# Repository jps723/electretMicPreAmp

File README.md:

# Electret Mic Preamp Build Notes 2/24/20

This project is in partnership with [Bantam Tools](https://www.bantamtools.com)

**Design Notes:**

This Electret Mic Preamp is a passive preamplifier and is based around the [LM358 op amp](https://www.ti.com/product/LM358).  This is a dual operational amplifier where in this circuit we are utilizing only one of the amplifiers on pins 1, 2, and 3.  Pin 4 is the Ground, where pin 8 is VCC.  

Pin 8 is powered by a 5v source, through two capacitors for filtering out high/low level noise (C2 and C3).  The electret mic is powered through a 10k resistor (R1), where the signal then goes through a coupling capacitor (C1) before a 1k resistor (R2) and entering pin 2.  A 200k variable resistor (VR1) serves to create feedback and the relationship between R2 and VR1 establishes the potential gain of the signal being represented by Gain = VR1/R2.  In this circuit, there is a potential gain of up to 200x the original signal (200k/1k = 200), allowing for a wide range of adjustment.

Two 100k resistors (R4/R5) are connected to GND and VCC respectively, prior to connecting to pin 3, for setting the potential voltage (2.5v). The circuit also has a power indicating LED for showing that the unit is powered on.

# Build Process
**Bits:**
1/32”
1/64”
**Mill Time:**
6m15s

It’s easiest to solder in this order:
```
1. Resistors
2. Ceramic Caps
3. Electret Mic
4. Dip Socket
5. LED
6. Electrolytic Caps
7. Screw Terminal
8. Potentiometer
```

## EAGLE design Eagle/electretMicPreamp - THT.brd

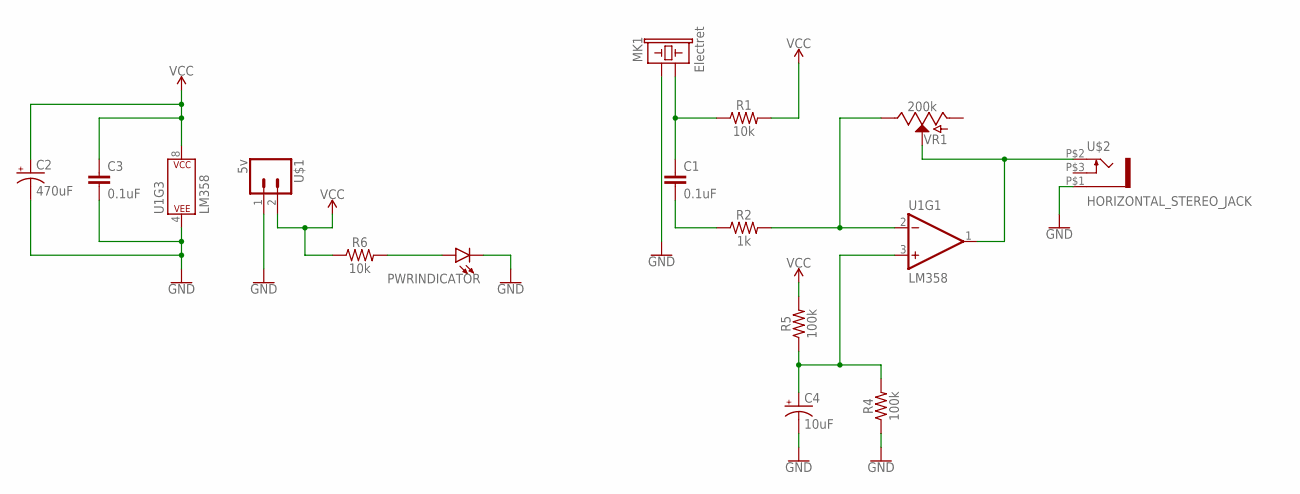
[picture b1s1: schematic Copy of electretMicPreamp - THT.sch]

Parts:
C1, C3: 0.1uF; CAP-PTH-SMALL-KIT
C2: 470uF; CPOL-RADIAL-2.5MM-5MM
C4: 10uF; CPOL-RADIAL-2.5MM-5MM
MK1: Electret; MICROPHONE-PTH-9.7MM
PWRINDICATOR: LED-3MM-NO_SILK; LED_3MM-NS
R1, R6: 10k; AXIAL-0.3
R2: 1k; AXIAL-0.3
R4, R5: 100k; AXIAL-0.3
U1: LM358; DIP08-KIT
U$1: 5v; SCREWTERMINAL-2X1
U$2: HORIZONTAL_STEREO_JACK
VR1: 200k; POT-PTH-ALPS

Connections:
GND: C2.2 (-), C3.2, C4.2 (-), MK1.1, PWRINDICATOR.K (C), R4.P$1 (1), U1.4 (P$V-), U$1.1, U$2.P$1 (1)
unnamed: C1.1, MK1.2, R1.P$1 (1)
unnamed: C1.2, R2.P$1 (1)
unnamed: R2.P$2 (2), U1.2 (-IN), VR1.P$1 (E)
unnamed: U1.1 (OUT), U$2.P$2 (2), VR1.P$2 (S)
unnamed: PWRINDICATOR.A, R6.P$2 (2)
unnamed: C4.1 (+), R4.P$2 (2), R5.P$1 (1), U1.3 (+IN)
VCC: C2.1 (+), C3.1, R1.P$2 (2), R5.P$2 (2), R6.P$1 (1), U1.8 (P$V+), U$1.2

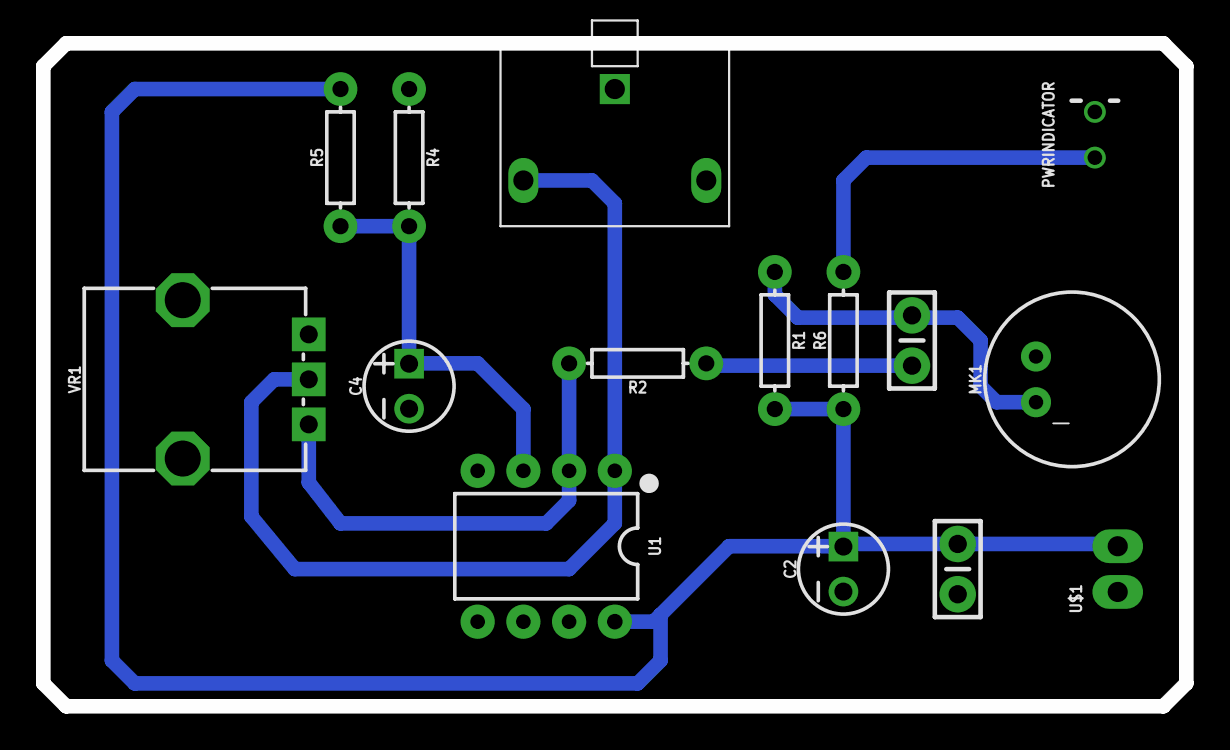
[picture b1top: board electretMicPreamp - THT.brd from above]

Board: 2 copper layers, 63.5 x 36.8 mm, 15 parts (0 on the bottom side), 8 nets.

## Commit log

2020-10-30 added bantam tools credit

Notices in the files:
parts and their libraries:
SparkFun-Retired: Licensing: Creative Commons ShareAlike 4.0 International - https://creativecommons.org/licenses/by-sa/4.0
